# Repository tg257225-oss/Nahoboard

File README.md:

# Nahoboard
A simple development board that allows the user to prototype, write code, and test hardware functions without needing to design a custom PCB. It is inspired by the protagonist of Atlus' Shin Megami Tensei V game (in their Aogami form).

Renders:
### 
### 

## Features (really standard stuff for a devboard)
* USB-C for easy connections
* A push button
* 12MHz Crystal

## Production
Everything in the 'Production' folder can be used to have this PCB manufactured by JLCPCB.

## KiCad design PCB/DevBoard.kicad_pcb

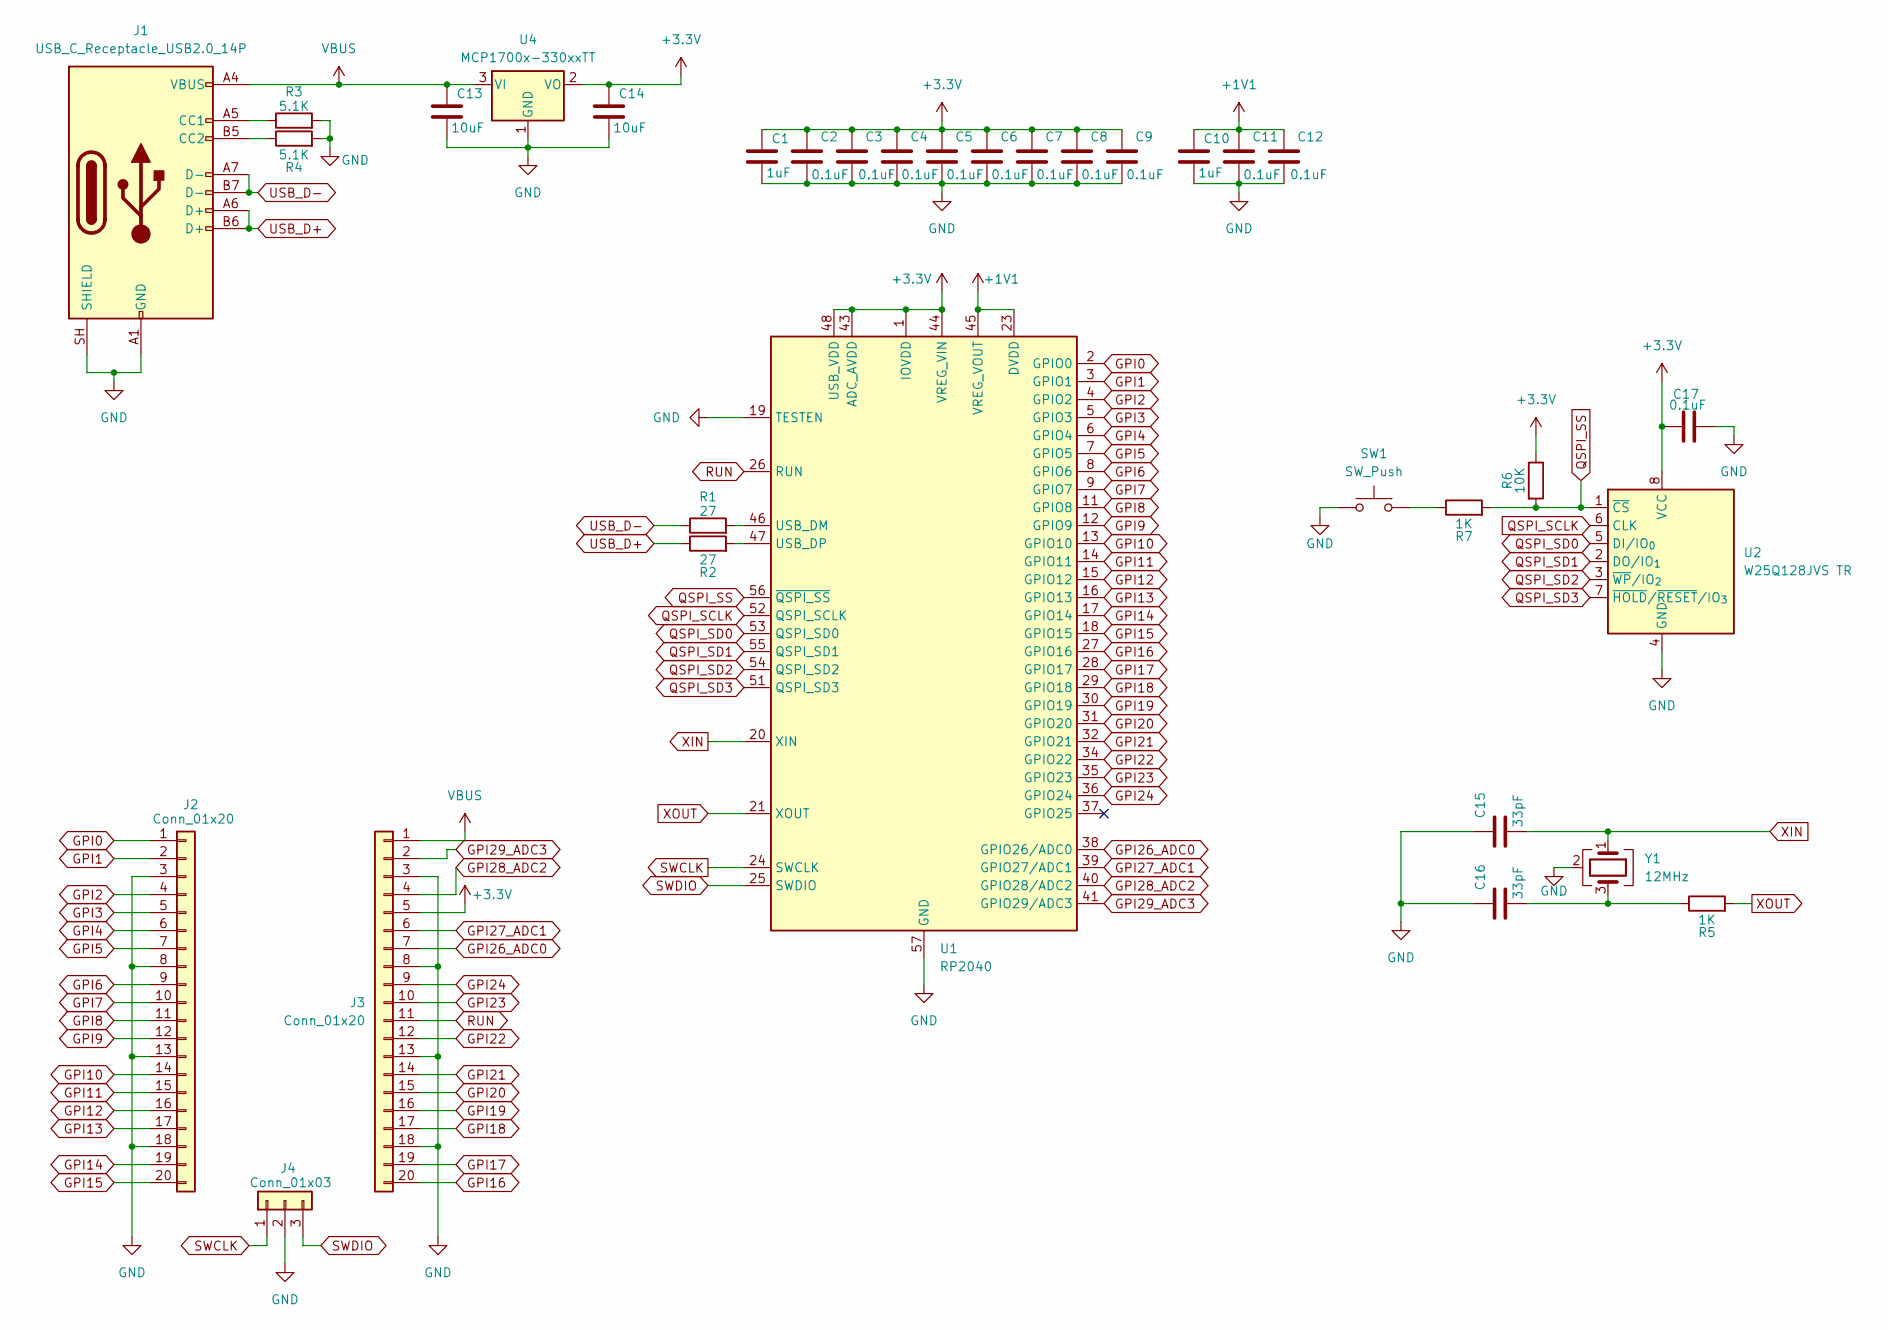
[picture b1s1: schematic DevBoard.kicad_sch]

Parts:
C1, C10: 1uF; C_0402_1005Metric
C2, C3, C4, C5, C6, C7, C8, C9, C11, C12, C17: 0.1uF; C_0402_1005Metric
C13, C14: 10uF; C_0603_1608Metric
C15, C16: 33pF; C_0402_1005Metric
J1: USB_C_Receptacle_USB2.0_14P; USB_C_Receptacle_HRO_TYPE-C-31-M-12
J2, J3: Conn_01x20; PinHeader_1x20_P2.54mm_Vertical
J4: Conn_01x03; PinHeader_1x03_P2.54mm_Vertical
R1, R2: 27; R_0402_1005Metric
R3, R4: 5.1K; R_0402_1005Metric
R5, R7: 1K; R_0402_1005Metric
R6: 10K; R_0402_1005Metric
SW1: SW_Push; SW_Push_SPST_NO_Alps_SKRK
U1: RP2040; QFN-56-1EP_7x7mm_P0.4mm_EP3.2x3.2mm
U2: W25Q128JVS TR; Winbond_USON-8-1EP_3x2mm_P0.5mm_EP0.2x1.6mm
U4: MCP1700x-330xxTT; SOT-23
Y1: 12MHz; Crystal_SMD_3225-4Pin_3.2x2.5mm

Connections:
+1V1: C10.1, C11.1, C12.1, U1.23 (DVDD), U1.45 (VREG_VOUT), U1.50 (DVDD)
+3.3V: C1.1, C2.1, C3.1, C4.1, C5.1, C6.1, C7.1, C8.1, C9.1, C14.1, C17.1, J3.5, R6.1, U1.1 (IOVDD), U1.10 (IOVDD), U1.22 (IOVDD), U1.33 (IOVDD), U1.42 (IOVDD), U1.43 (ADC_AVDD), U1.44 (VREG_VIN), U1.48 (USB_VDD), U1.49 (IOVDD), U2.8 (VCC), U4.2 (VO)
GND: C1.2, C2.2, C3.2, C4.2, C5.2, C6.2, C7.2, C8.2, C9.2, C10.2, C11.2, C12.2, C13.2, C14.2, C15.1, C16.1, C17.2, J1.A1 (GND), J1.A12 (GND), J1.B1 (GND), J1.B12 (GND), J1.SH (SHIELD), J2.3, J2.8, J2.13, J2.18, J3.3, J3.8, J3.13, J3.18, J4.2, R3.2, R4.2, SW1.1, U1.19 (TESTEN), U1.57 (GND), U2.4 (GND), U4.1 (GND), Y1.2 (G), Y1.4 (G)
GPI0: J2.1, U1.2 (GPIO0)
GPI1: J2.2, U1.3 (GPIO1)
GPI2: J2.4, U1.4 (GPIO2)
GPI3: J2.5, U1.5 (GPIO3)
GPI4: J2.6, U1.6 (GPIO4)
GPI5: J2.7, U1.7 (GPIO5)
GPI6: J2.9, U1.8 (GPIO6)
GPI7: J2.10, U1.9 (GPIO7)
GPI8: J2.11, U1.11 (GPIO8)
GPI9: J2.12, U1.12 (GPIO9)
GPI10: J2.14, U1.13 (GPIO10)
GPI11: J2.15, U1.14 (GPIO11)
GPI12: J2.16, U1.15 (GPIO12)
GPI13: J2.17, U1.16 (GPIO13)
GPI14: J2.19, U1.17 (GPIO14)
GPI15: J2.20, U1.18 (GPIO15)
GPI16: J3.20, U1.27 (GPIO16)
GPI17: J3.19, U1.28 (GPIO17)
GPI18: J3.17, U1.29 (GPIO18)
GPI19: J3.16, U1.30 (GPIO19)
GPI20: J3.15, U1.31 (GPIO20)
GPI21: J3.14, U1.32 (GPIO21)
GPI22: J3.12, U1.34 (GPIO22)
GPI23: J3.10, U1.35 (GPIO23)
GPI24: J3.9, U1.36 (GPIO24)
GPI26_ADC0: J3.7, U1.38 (GPIO26/ADC0)
GPI27_ADC1: J3.6, U1.39 (GPIO27/ADC1)
GPI28_ADC2: J3.4, U1.40 (GPIO28/ADC2)
GPI29_ADC3: J3.2, U1.41 (GPIO29/ADC3)
unnamed: C16.2, R5.1, Y1.3
unnamed: J1.A5 (CC1), R3.1
unnamed: J1.B5 (CC2), R4.1
unnamed: R7.1, SW1.2
unnamed: R1.2, U1.46 (USB_DM)
unnamed: R2.2, U1.47 (USB_DP)
QSPI_SCLK: U1.52 (QSPI_SCLK), U2.6 (CLK)
QSPI_SD0: U1.53 (QSPI_SD0), U2.5 (DI/IO_{0})
QSPI_SD1: U1.55 (QSPI_SD1), U2.2 (DO/IO_{1})
QSPI_SD2: U1.54 (QSPI_SD2), U2.3 (~WP/IO_{2})
QSPI_SD3: U1.51 (QSPI_SD3), U2.7 (~HOLD/~RESET/IO_{3})
QSPI_SS: R6.2, R7.2, U1.56 (~QSPI_SS), U2.1 (~CS)
RUN: J3.11, U1.26 (RUN)
SWCLK: J4.1, U1.24 (SWCLK)
SWDIO: J4.3, U1.25 (SWDIO)
USB_D+: J1.A6 (D+), J1.B6 (D+), R2.1
USB_D-: J1.A7 (D-), J1.B7 (D-), R1.1
VBUS: C13.1, J1.A4 (VBUS), J1.A9 (VBUS), J1.B4 (VBUS), J1.B9 (VBUS), J3.1, U4.3 (VI)
XIN: C15.2, U1.20 (XIN), Y1.1
XOUT: R5.2, U1.21 (XOUT)

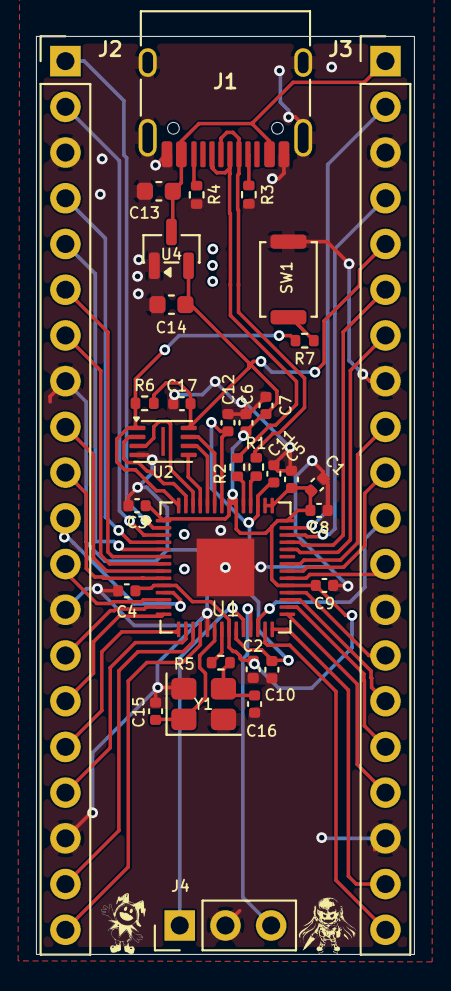
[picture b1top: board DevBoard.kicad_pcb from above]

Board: 2 copper layers, 21.0 x 51.0 mm, 33 parts (0 on the bottom side), 52 nets.

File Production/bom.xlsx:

Item | Qty | Reference | Value | Est. Unit Price | Est. Extended Price
1.0 | 2.0 | C1, C10 | 1μF | 0.05 | 0.1
2.0 | 11.0 | C2-C9, C11, C12, C17 | 0.1μF | 0.05 | 0.55
3.0 | 2.0 | C13, C14 | 10μF | 0.05 | 0.1
4.0 | 2.0 | C15, C16 | 33pF | 0.05 | 0.1
5.0 | 1.0 | J1 | USB-C 2.0 | 0.6 | 0.6
6.0 | 2.0 | J2, J3 | 20-pin Header | 0.4 | 0.8
7.0 | 1.0 | J4 | 3-pin Header | 0.15 | 0.15
8.0 | 2.0 | R1, R2 | 27Ω | 0.05 | 0.1
9.0 | 2.0 | R3, R4 | 5.1kΩ | 0.05 | 0.1
10.0 | 2.0 | R5, R7 | 1kΩ | 0.05 | 0.1
11.0 | 1.0 | R6 | 10kΩ | 0.05 | 0.05
12.0 | 1.0 | SW1 | Push Button | 0.25 | 0.25
13.0 | 1.0 | U1 (RP2040) | Microcontroller | 0.92 | 0.92
14.0 | 1.0 | U2 | 128Mbit Flash | 3.72 | 3.72
15.0 | 1.0 | U4 | 3.3V LDO | 0.51 | 0.51
16.0 | 1.0 | Y1 | 12MHz Crystal | 0.3 | 0.3
Total | 33.0 |  |  |  | 8.45
